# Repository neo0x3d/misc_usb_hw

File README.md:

# misc_usb_hw

# This project has been moved to Gitlab: <https://gitlab.com/users/neo0x3d/projects>

Misc (passive) USB hardware

## usb_interceptor
Allows to intercept GND and 5V rail for power measurements.

## usb_condom_extended_v1
Basic USB condom extended functionality (optional disconnect D+ and D-, voltage divider on output).
Optional reverse polarity protection, over current protection (polyfuse + NCP361) and over voltage protection (NCP361)

## note:
Silkscreen will show sometimes 0x3d instead of neo0x3d. There is no correlation with github user 0x3d.

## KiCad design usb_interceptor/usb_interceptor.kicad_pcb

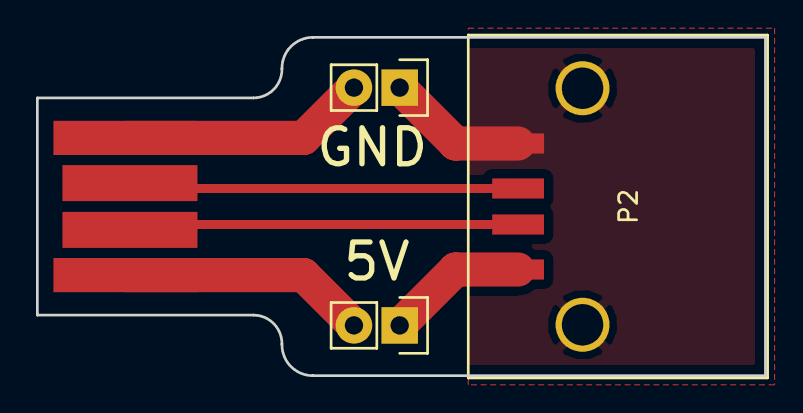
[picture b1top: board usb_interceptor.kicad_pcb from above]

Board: 2 copper layers, 40.4 x 18.8 mm, 4 parts (0 on the bottom side), 6 nets.

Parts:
5V: Jumper_NO_Small; Pin_Header_Straight_1x02
GND: Jumper_NO_Small; Pin_Header_Straight_1x02
P1: USB_A; usb_pcb_in
P2: USB_A; usb_smd_tht_combo

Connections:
unnamed: GND.1, P2.4, P2.5, P2.6
unnamed: GND.2, P1.4
unnamed: 5V.1, P2.1
unnamed: 5V.2, P1.1
unnamed: P1.2, P2.2
unnamed: P1.3, P2.3

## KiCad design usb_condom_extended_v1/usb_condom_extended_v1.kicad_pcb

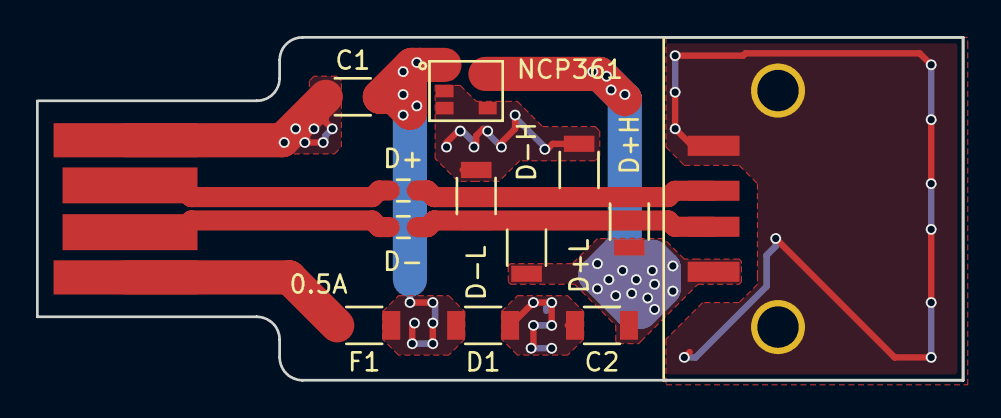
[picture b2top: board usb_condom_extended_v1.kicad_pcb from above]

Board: 2 copper layers, 51.4 x 19.1 mm, 13 parts (0 on the bottom side), 8 nets.

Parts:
C1, C2: 1µF,25V,x5r; C_1206
D1: D; C_1206
D+: Jumper_NC_Small; C_0603
D+H: R; R_1206
D+L: R; R_1206
D-: Jumper_NC_Small; C_0603
D-H: R; R_1206
D-L: R; R_1206
F1: 0.5A; C_1206
NCP361: NCP361; ncp361_tsop5
P1: USB_A; usb_smd_tht_combo
USB_in1: usb_connector; usb_pcb_in

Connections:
D_out+: D+.2, D+H.2, D+L.1, P1.3
D_out-: D-.2, D-H.2, D-L.1, P1.2
D_pre+: D+.1, USB_in1.3
D_pre-: D-.1, USB_in1.2
GND: C1.2, C2.2, D1.2, D+L.2, D-L.2, NCP361.2, NCP361.3, NCP361.4, P1.4, P1.5, P1.6, USB_in1.4
unnamed: F1.2, USB_in1.1
VBUS_in: C1.1, D1.1, F1.1, NCP361.1
VBUS_out: C2.1, D+H.1, D-H.1, NCP361.5, P1.1

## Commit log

2016-08-23 initial commit with usb_interceptor and usb_condom_extended_v1
2016-08-23 initial commit of README.md file
2017-03-10 changed to gitlab
